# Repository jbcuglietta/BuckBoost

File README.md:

# BuckBoost

Overview
--------

Eagle CAD schematic file for a buck/boost converter for LiPo batteries, can buck/boost to voltages between 1.2 and 5.5V depending on the resistor configuration you choose. 

- Quick start manual included for setup
- Designed to fit on a standard breakout board for easy prototyping

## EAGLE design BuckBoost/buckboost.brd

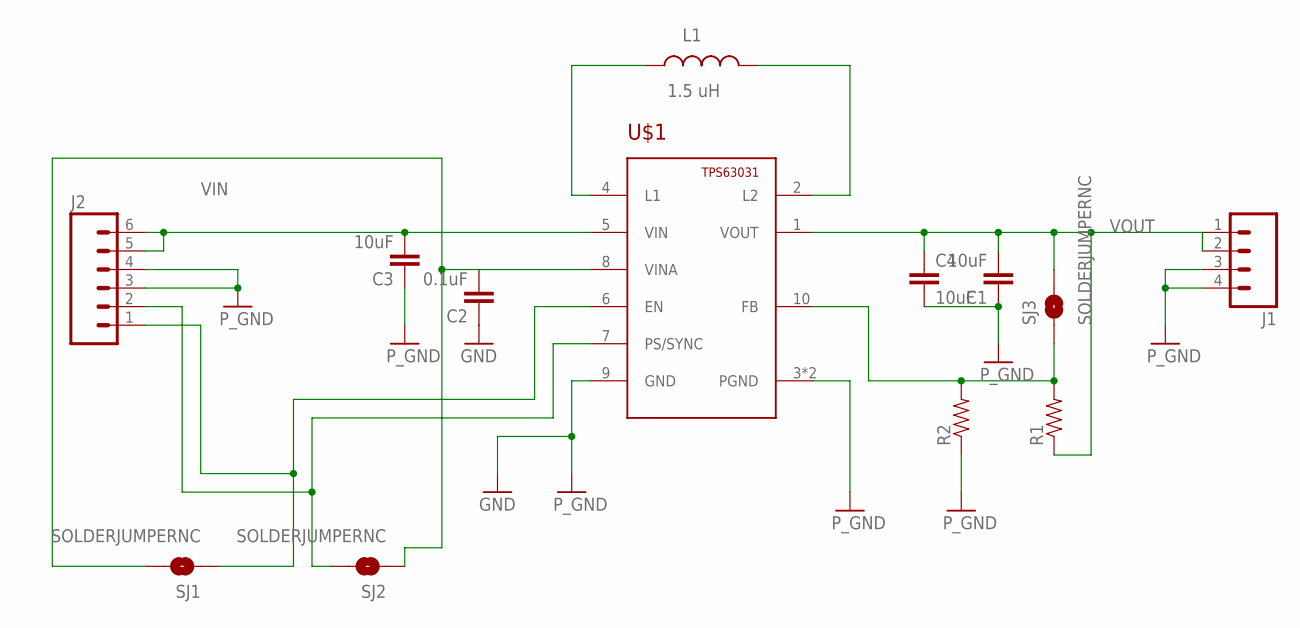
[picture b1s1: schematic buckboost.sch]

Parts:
C1, C3, C4: 10uF; 1206
C2: 0.1uF; 1206
J1: M04PTH; 1X04
J2: M06SILK_FEMALE_PTH; 1X06
L1: 1.5 uH; IND1212
R1, R2: RESISTOR1206; 1206
SJ1, SJ2, SJ3: SOLDERJUMPERNC; SJ_2S
U$1: TPS63031; SON-10

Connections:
GND: C1.1, C2.1, C3.1, C4.2, J1.3, J1.4, J2.3, J2.4, R2.1, U$1.3 (PGND), U$1.9 (GND), U$1.PAD (PGND)
L1: L1.P$1 (1), U$1.4 (L1)
L2: L1.P$2 (2), U$1.2 (L2)
unnamed: R1.2, R2.2, SJ3.1, U$1.10 (FB)
unnamed: C2.2, SJ1.2, SJ2.1, U$1.8 (VINA)
unnamed: J2.2, SJ2.2, U$1.7 (PS/SYNC)
unnamed: J2.1, SJ1.1, U$1.6 (EN)
VIN: C3.2, J2.5, J2.6, U$1.5 (VIN)
VOUT: C1.2, C4.1, J1.1, J1.2, R1.1, SJ3.2, U$1.1 (VOUT)

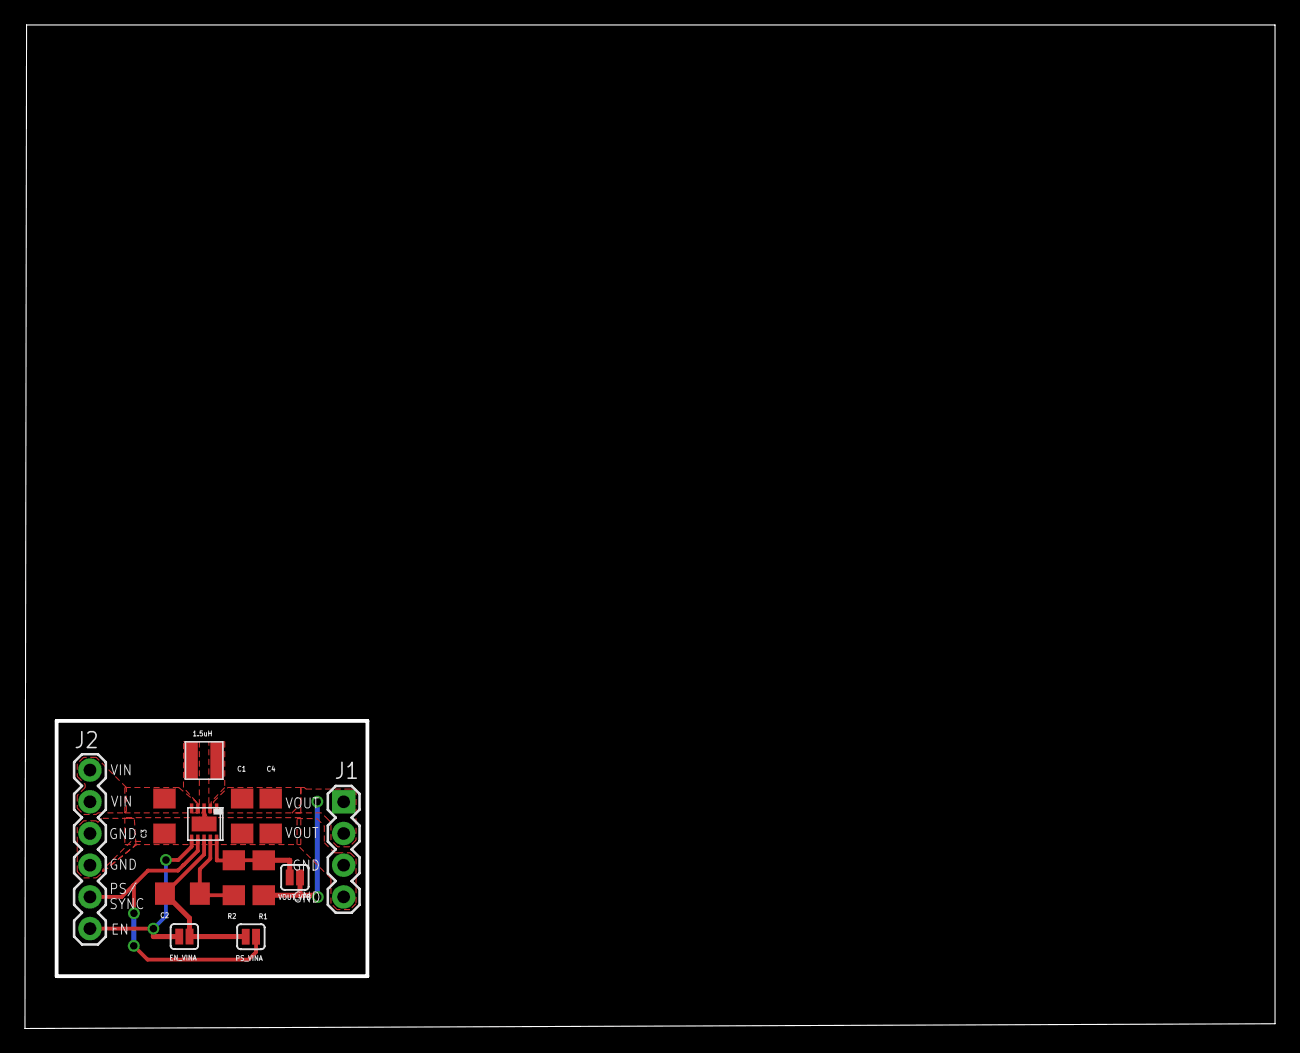
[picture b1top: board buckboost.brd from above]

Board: 2 copper layers, 100.1 x 80.4 mm, 13 parts (0 on the bottom side), 9 nets.

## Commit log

2016-02-22 Changed Resistor and Capacity sizes
2016-02-22 PCB finished, only need to fix labels
2016-02-22 Headers Aligned for breadBoard
2016-02-22 Finshed VOUT, just labels
2016-02-22 added 6 header
2016-02-22 integrated 6 pin header
2016-02-22 Added silk to the board for breakout
2016-02-23 Added Jumpers
2016-02-23 Added vout_vfb jumper
2016-02-23 moved fb_vout jumper
2016-05-09 Added Quick Start Manual

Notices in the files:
parts and their libraries:
SparkFun-Resistors: Licensing: Creative Commons ShareAlike 4.0 International - https://creativecommons.org/licenses/by-sa/4.0
